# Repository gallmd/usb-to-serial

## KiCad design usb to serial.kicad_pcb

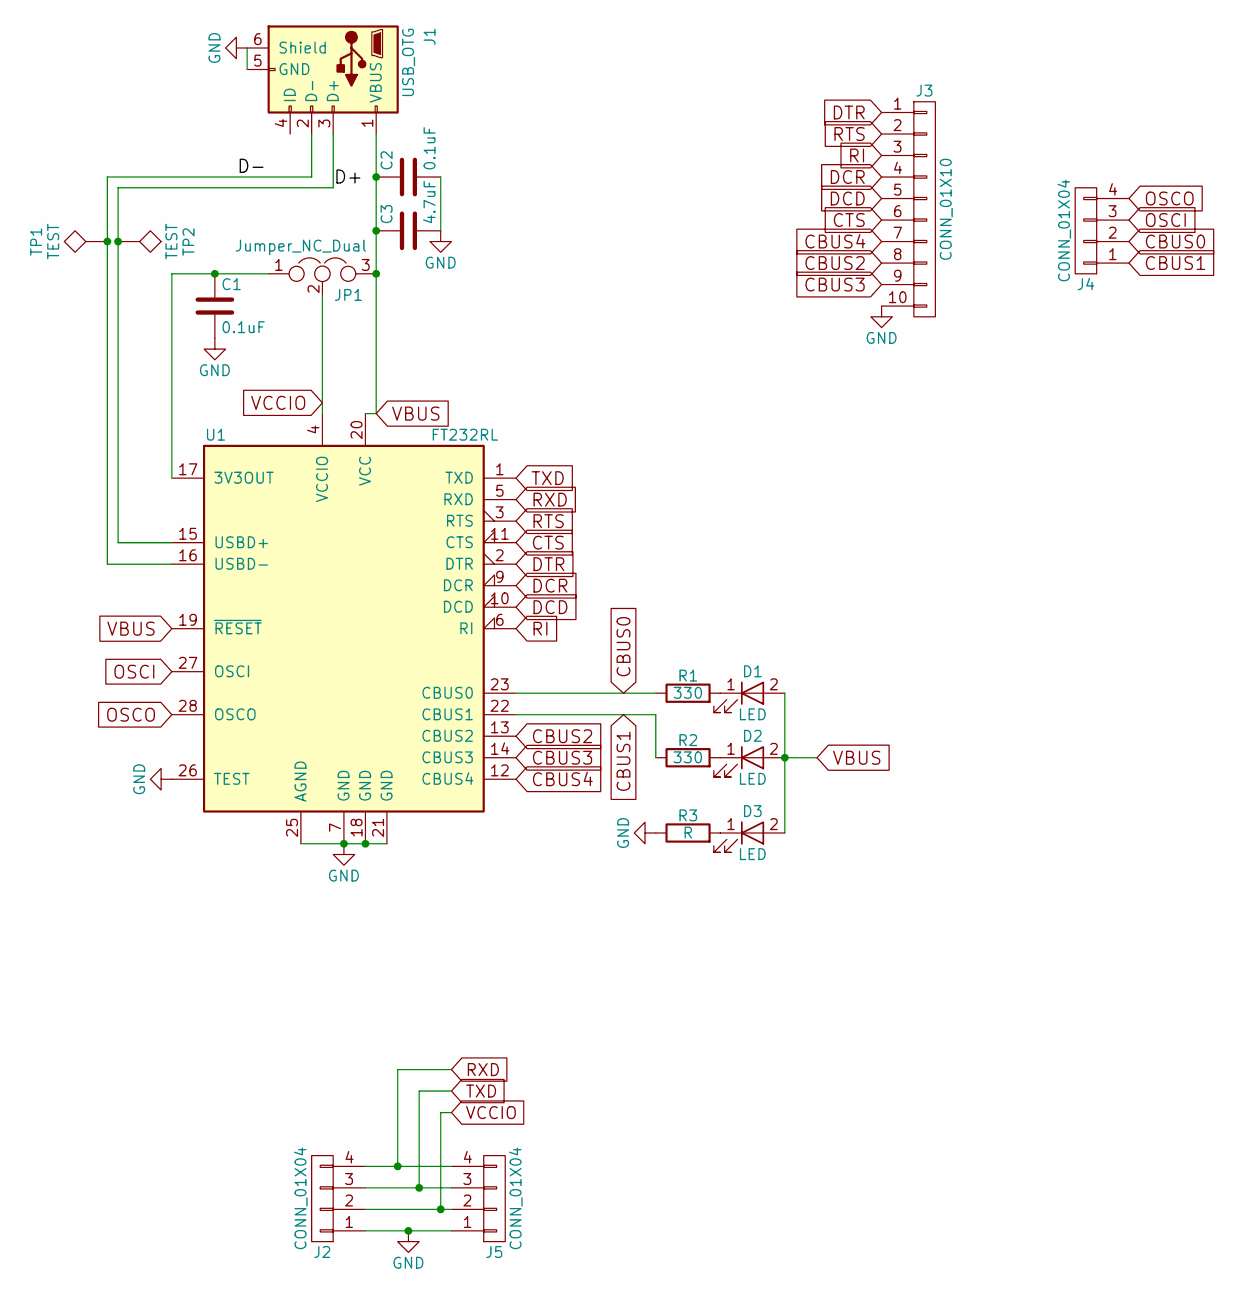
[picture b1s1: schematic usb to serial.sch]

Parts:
C1, C2: 0.1uF; C_1206_HandSoldering
C3: 4.7uF; C_1206_HandSoldering
D1, D2, D3: LED; LED_1206_HandSoldering
J1: USB_OTG; USB_Mini-B
J2, J4, J5: CONN_01X04; Pin_Header_Straight_1x04_Pitch2.54mm
J3: CONN_01X10; Pin_Header_Straight_1x10_Pitch2.54mm
JP1: Jumper_NC_Dual; Pin_Header_Straight_1x03_Pitch2.54mm
R1, R2: 330; R_1206_HandSoldering
R3: R; R_1206_HandSoldering
TP1, TP2: TEST; test_point
U1: FT232RL; SSOP-28_5.3x10.2mm_Pitch0.65mm

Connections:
/D+: J1.3 (D+), TP2.1, U1.15 (USBD+)
/D-: J1.2 (D-), TP1.1, U1.16 (USBD-)
CBUS0: J4.2, R1.1, U1.23 (CBUS0)
CBUS1: J4.1, R2.1, U1.22 (CBUS1)
CBUS2: J3.8, U1.13 (CBUS2)
CBUS3: J3.9, U1.14 (CBUS3)
CBUS4: J3.7, U1.12 (CBUS4)
CTS: J3.6, U1.11 (CTS)
DCD: J3.5, U1.10 (DCD)
DCR: J3.4, U1.9 (DCR)
DTR: J3.1, U1.2 (DTR)
GND: C1.2, C2.2, C3.2, J1.5 (GND), J1.6 (Shield), J2.1, J3.10, J5.1, R3.1, U1.7 (GND), U1.18 (GND), U1.21 (GND), U1.25 (AGND), U1.26 (TEST)
unnamed: C1.1, JP1.1, U1.17 (3V3OUT)
unnamed: D1.1 (K), R1.2
unnamed: D2.1 (K), R2.2
unnamed: D3.1 (K), R3.2
OSCI: J4.3, U1.27 (OSCI)
OSCO: J4.4, U1.28 (OSCO)
RI: J3.3, U1.6 (RI)
RTS: J3.2, U1.3 (RTS)
RXD: J2.4, J5.4, U1.5 (RXD)
TXD: J2.3, J5.3, U1.1 (TXD)
VBUS: C2.1, C3.1, D1.2 (A), D2.2 (A), D3.2 (A), J1.1 (VBUS), JP1.3, U1.19 (~RESET~), U1.20 (VCC)
VCCIO: J2.2, J5.2, JP1.2, U1.4 (VCCIO)

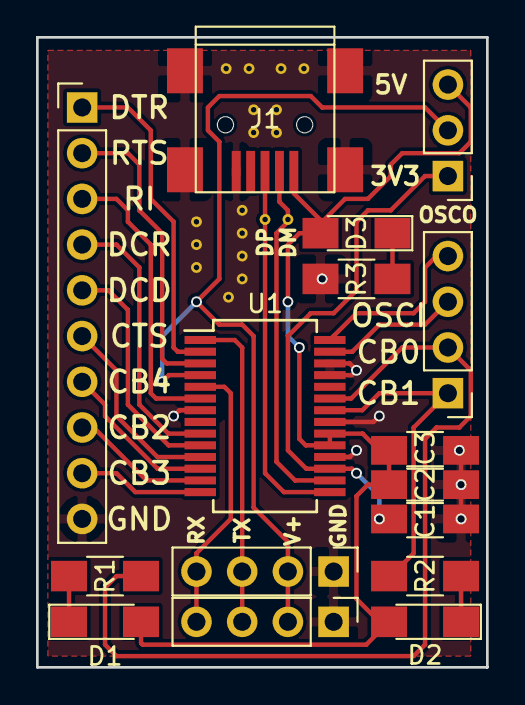
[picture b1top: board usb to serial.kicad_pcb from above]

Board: 2 copper layers, 25.0 x 35.0 mm, 18 parts (0 on the bottom side), 24 nets.

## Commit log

2019-07-15 Released version of board
2019-07-15 Release version 1.0.0
